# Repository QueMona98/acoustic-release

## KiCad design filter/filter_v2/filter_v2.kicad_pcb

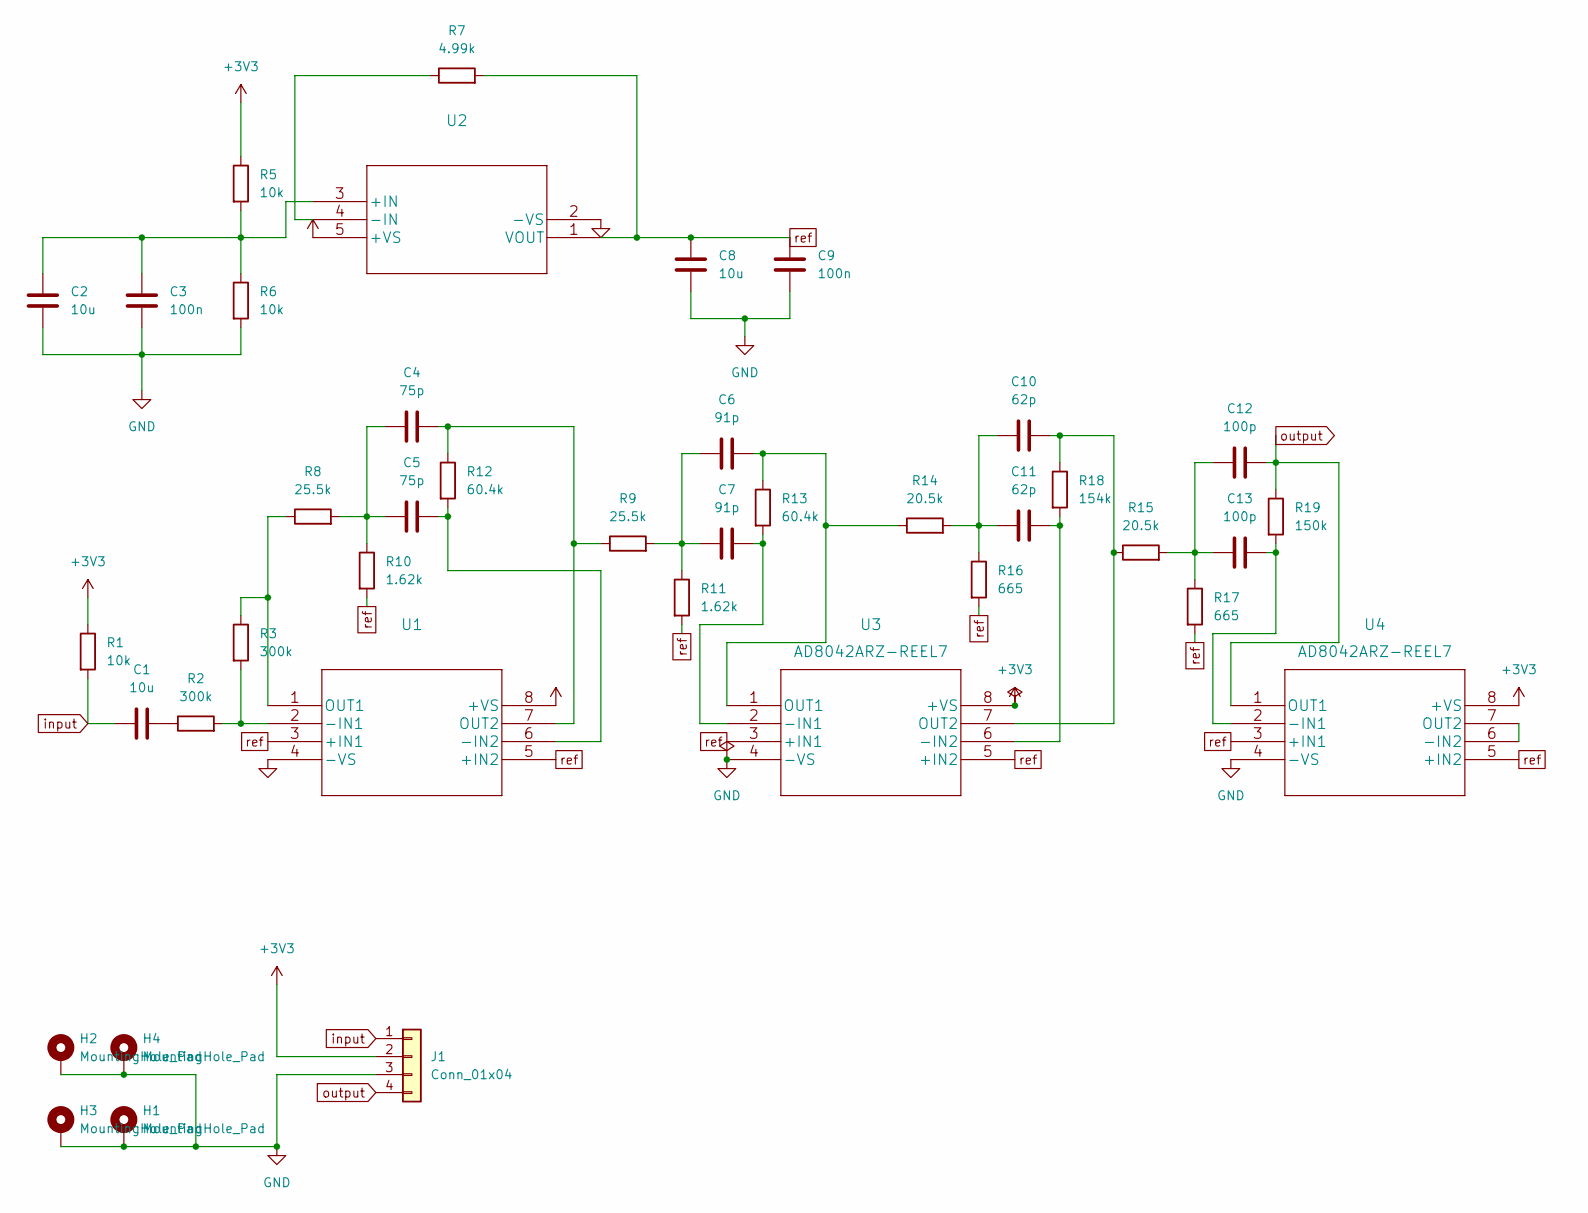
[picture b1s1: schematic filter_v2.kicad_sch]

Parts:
C1, C2, C8: 10u; C_0805_2012Metric
C3, C9: 100n; C_0402_1005Metric
C4, C5: 75p; C_0402_1005Metric
C6, C7: 91p; C_0402_1005Metric
C10, C11: 62p; C_0402_1005Metric
C12, C13: 100p; C_0402_1005Metric
H1, H2, H3, H4: MountingHole_Pad; MountingHole_2.2mm_M2_DIN965_Pad
J1: Conn_01x04; FanPinHeader_1x04_P2.54mm_Vertical
R1, R5, R6: 10k
R2, R3: 300k; R_Axial_DIN0207_L6.3mm_D2.5mm_P10.16mm_Horizontal
R7: 4.99k
R8, R9: 25.5k
R10, R11: 1.62k
R12, R13: 60.4k
R14, R15: 20.5k
R16, R17: 665
R18: 154k
R19: 150k
U1, U2: (no value)
U3, U4: AD8042ARZ-REEL7

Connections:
unnamed: C1.1, R2.1
unnamed: C2.1, C3.1, R5.2, R6.1, U2.3 (+IN)
unnamed: C4.1, C5.1, R8.2, R10.1
unnamed: C4.2, R9.1, R12.1, U1.7 (OUT2)
unnamed: C5.2, R12.2, U1.6 (-IN2)
unnamed: C6.1, C7.1, R9.2, R11.1
unnamed: C6.2, R13.1, R14.1, U3.1 (OUT1)
unnamed: C7.2, R13.2, U3.2 (-IN1)
unnamed: C10.1, C11.1, R14.2, R16.1
unnamed: C10.2, R15.1, R18.1, U3.7 (OUT2)
unnamed: C11.2, R18.2, U3.6 (-IN2)
unnamed: C12.1, C13.1, R15.2, R17.1
unnamed: C13.2, R19.2, U4.2 (-IN1)
unnamed: R2.2, R3.2, U1.2 (-IN1)
unnamed: R7.1, U2.4 (-IN)
unnamed: R3.1, R8.1, U1.1 (OUT1)
unnamed: U4.6 (-IN2), U4.7 (OUT2)
input: C1.2, J1.1, R1.2
output: C12.2, J1.4, R19.1, U4.1 (OUT1)
ref: C8.1, C9.1, R7.2, R10.2, R11.2, R16.2, R17.2, U1.3 (+IN1), U1.5 (+IN2), U2.1 (VOUT), U3.3 (+IN1), U3.5 (+IN2), U4.3 (+IN1), U4.5 (+IN2)

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
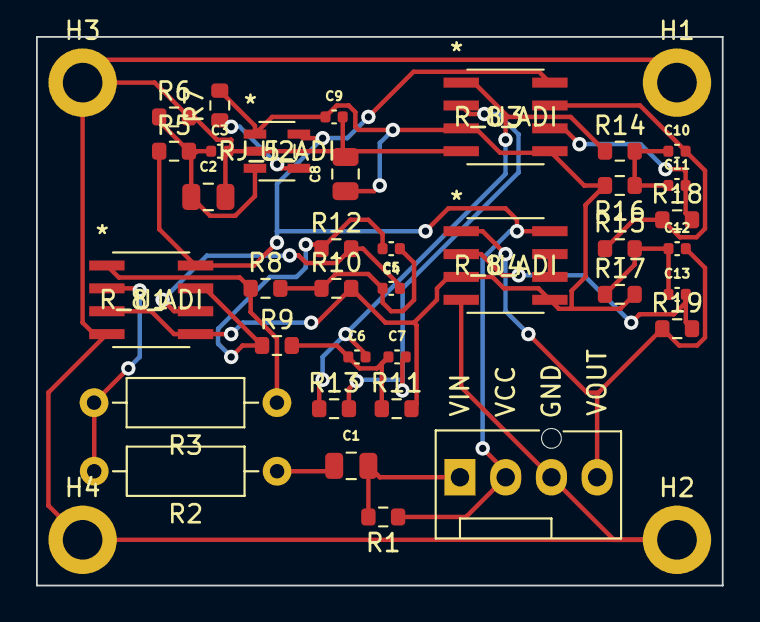
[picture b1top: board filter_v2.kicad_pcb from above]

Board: 2 copper layers, 38.1 x 30.5 mm, 40 parts (0 on the bottom side), 22 nets.

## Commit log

2023-01-16 initialized repo

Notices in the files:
parts and their libraries:
Copyright 2021 Accelerated Designs. All rights reserved.
